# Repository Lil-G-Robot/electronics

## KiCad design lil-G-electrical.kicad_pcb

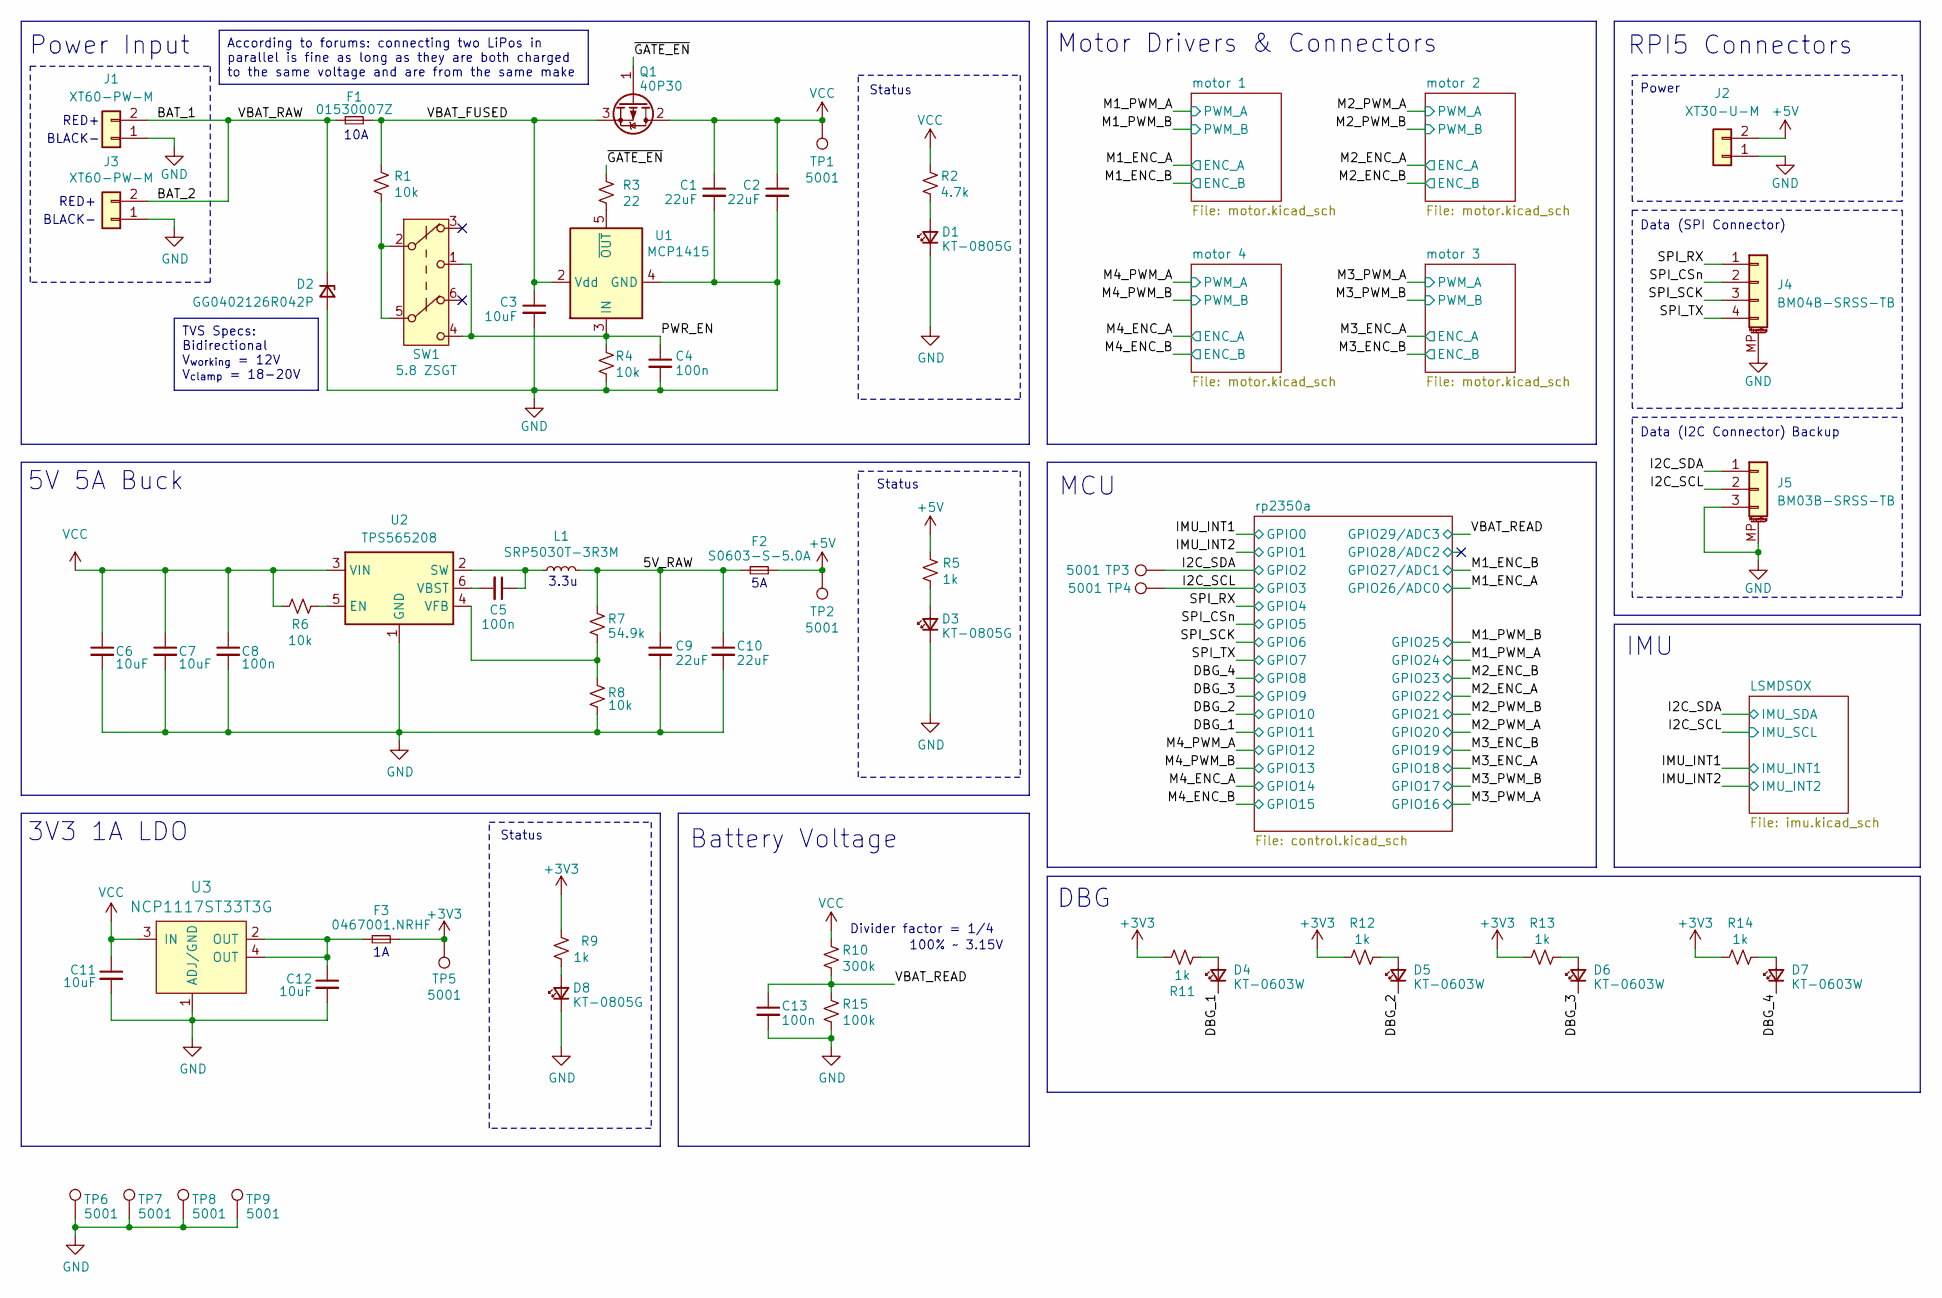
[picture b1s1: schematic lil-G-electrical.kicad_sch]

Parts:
C1, C2, C9, C10: 22uF; C_0805_2012Metric
C3, C6, C7, C11, C12: 10uF; C_0603_1608Metric
C4, C5, C8, C13: 100n; C_0402_1005Metric
D1, D3, D8: KT-0805G; LED_0805_2012Metric
D2: GG0402126R042P; D_0402_1005Metric
D4, D5, D6, D7: KT-0603W; LED_0603_1608Metric
F1: 01530007Z; LittleFuse_01530007Z
F2: S0603-S-5.0A; Fuse_0603_1608Metric; MPN F0603SB5000V032TM
F3: 0467001.NRHF; Fuse_0603_1608Metric; MPN F0603SB5000V032TM
J1, J3: XT60-PW-M; AMASS_XT60PW-M_1x02_P7.20mm_Horizontal
J2: XT30-U-M; AMASS_XT30U-M_1x02_P5.0mm_Vertical
J4: BM04B-SRSS-TB; JST_SH_BM04B-SRSS-TB_1x04-1MP_P1.00mm_Vertical
J5: BM03B-SRSS-TB; JST_SH_BM03B-SRSS-TB_1x03-1MP_P1.00mm_Vertical
L1: SRP5030T-3R3M; L_Bourns_SRP5030T; MPN SRP5030T-3R3M
Q1: 40P30; TO-252-2
R1, R4, R6, R8: 10k; R_0402_1005Metric
R2: 4.7k; R_0402_1005Metric
R3: 22; R_0402_1005Metric
R5, R9, R11, R12, R13, R14: 1k; R_0402_1005Metric
R7: 54.9k; R_0402_1005Metric
R10: 300k; R_0603_1608Metric
R15: 100k; R_0603_1608Metric
SW1: 5.8 ZSGT; 5.8_ZSGT
TP1, TP2, TP3, TP4, TP5, TP6, TP7, TP8, TP9: 5001; TestPoint_Keystone_5000-5004_Miniature
U1: MCP1415; SOT-23-5
U2: TPS565208; SOT-23-6
U3: NCP1117ST33T3G; SOT-223; MPN NCP1117ST33T3G

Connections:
+3V3: F3.2, R9.2, R11.1, R12.2, R13.2, R14.2, TP5.1; also elsewhere on the board
+5V: F2.2, J2.2, R5.2, TP2.1; also elsewhere on the board
/5V_RAW: C9.1, C10.1, F2.1, L1.2, R7.2
/BAT_1: D2.1 (K), F1.1, J1.2, J3.2
/DBG_1: D4.1 (K); also elsewhere on the board
/DBG_2: D5.1 (K); also elsewhere on the board
/DBG_3: D6.1 (K); also elsewhere on the board
/DBG_4: D7.1 (K); also elsewhere on the board
/I2C_SCL: J5.2, TP4.1; also elsewhere on the board
/I2C_SDA: J5.1, TP3.1; also elsewhere on the board
/PWR_EN: C4.1, R4.1, SW1.1 (C), SW1.4 (C), U1.3 (IN)
/SPI_CSn: J4.2; also elsewhere on the board
/SPI_RX: J4.1; also elsewhere on the board
/SPI_SCK: J4.3; also elsewhere on the board
/SPI_TX: J4.4; also elsewhere on the board
/VBAT_FUSED: C3.1, F1.2, Q1.3 (S), R1.1, U1.2 (Vdd)
/VBAT_READ: C13.1, R10.1, R15.2; also elsewhere on the board
/~GATE_EN: Q1.1 (G), R3.1
GND: C1.2, C2.2, C3.2, C4.2, C6.2, C7.2, C8.2, C9.2, C10.2, C11.2, C12.2, C13.2, D1.1 (K), D2.2 (A), D3.1 (K), D8.1 (K), J1.1, J2.1, J3.1, J4.MP (MountPin), J5.3, J5.MP (MountPin), R4.2, R8.1, R15.1, TP6.1, TP7.1, TP8.1, TP9.1, U1.4 (GND), U2.1 (GND), U3.1 (ADJ/GND); also elsewhere on the board
unnamed: C12.1, F3.1, U3.2 (OUT), U3.4 (OUT)
unnamed: D1.2 (A), R2.1
unnamed: D3.2 (A), R5.1
unnamed: D4.2 (A), R11.2
unnamed: D5.2 (A), R12.1
unnamed: D6.2 (A), R13.1
unnamed: D7.2 (A), R14.1
unnamed: D8.2 (A), R9.1
unnamed: R1.2, SW1.2 (B), SW1.5 (B)
unnamed: R3.2, U1.5 (~OUT)
unnamed: R6.1, U2.5 (EN)
unnamed: C5.1, L1.1, U2.2 (SW)
unnamed: C5.2, U2.6 (VBST)
unnamed: R7.1, R8.2, U2.4 (VFB)
VCC: C1.1, C2.1, C6.1, C7.1, C8.1, C11.1, Q1.2 (D), R2.2, R6.2, R10.2, TP1.1, U2.3 (VIN), U3.3 (IN); also elsewhere on the board

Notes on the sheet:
According to forums: connecting two LiPos in parallel is fine as long as they are both charged to the same voltage and are from the same make
TVS Specs: Bidirectional V_{working} = 12V V_{clamp} = 18-20V
RPI5 Connectors
IMU
Status
MCU
Data (SPI Connector)
5V 5A Buck
BLACK-
Divider factor = 1/4
100% ~ 3.15V
Power
Data (I2C Connector)
Battery Voltage
Motor Drivers & Connectors
Power Input
DBG
3V3 1A LDO
10A
RED+
Backup
3.3u

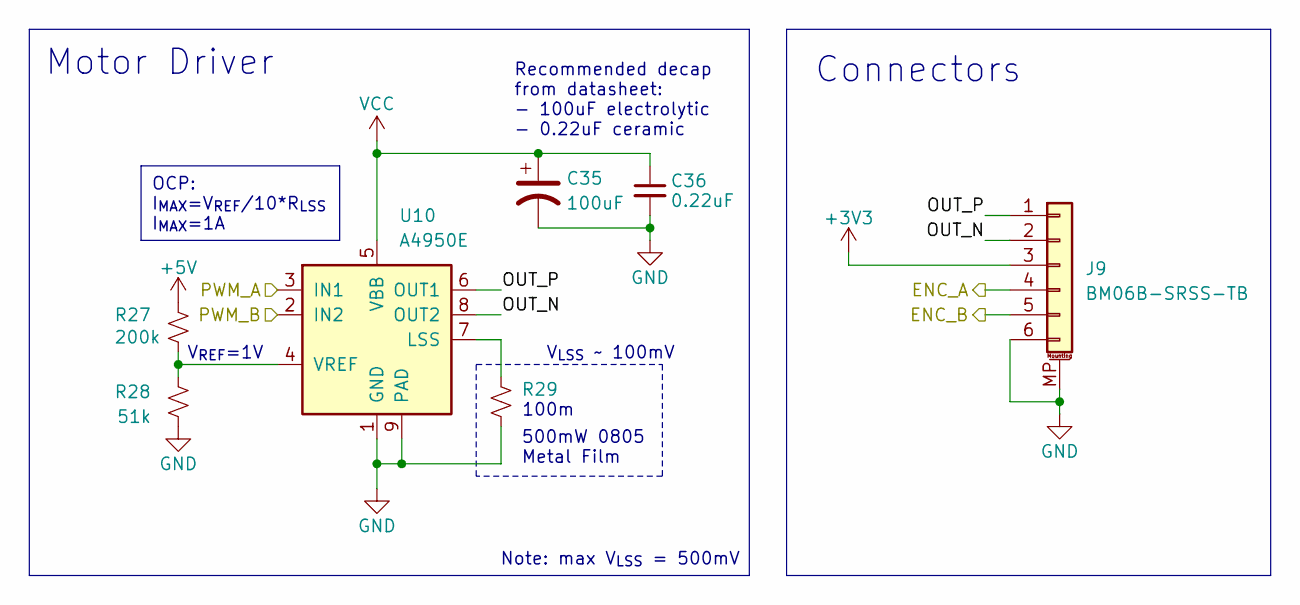
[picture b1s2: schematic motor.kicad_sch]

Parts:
C35: 100uF; CP_Elec_6.3x7.7
C36: 0.22uF; C_0603_1608Metric
J9: BM06B-SRSS-TB; JST_SH_BM06B-SRSS-TB_1x06-1MP_P1.00mm_Vertical
R27: 200k; R_0402_1005Metric
R28: 51k; R_0402_1005Metric
R29: RL10FTNR100; R_0805_2012Metric
U10: A4950E; SOIC-8-1EP_3.9x4.9mm_P1.27mm_EP2.41x3.3mm_ThermalVias

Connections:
+3V3: J9.3; also elsewhere on the board
+5V: R27.2; also elsewhere on the board
/M1_ENC_A: J9.4; also elsewhere on the board
/M1_ENC_B: J9.5; also elsewhere on the board
/M1_PWM_A: U10.3 (IN1); also elsewhere on the board
/M1_PWM_B: U10.2 (IN2); also elsewhere on the board
/motor 1/OUT_N: J9.2, U10.8 (OUT2)
/motor 1/OUT_P: J9.1, U10.6 (OUT1)
GND: C35.2, C36.2, J9.6, J9.MP (MountPin), R28.1, R29.2, U10.1 (GND), U10.9 (PAD); also elsewhere on the board
unnamed: R29.1, U10.7 (LSS)
unnamed: R27.1, R28.2, U10.4 (VREF)
VCC: C35.1, C36.1, U10.5 (VBB); also elsewhere on the board

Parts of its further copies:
C37, C39, C41: 100uF; CP_Elec_6.3x7.7
C38, C40, C42: 0.22uF; C_0603_1608Metric
J10, J11, J12: BM06B-SRSS-TB; JST_SH_BM06B-SRSS-TB_1x06-1MP_P1.00mm_Vertical
R30, R33, R36: 200k; R_0402_1005Metric
R32, R35, R38: RL10FTNR100; R_0805_2012Metric
U11, U12, U13: A4950E; SOIC-8-1EP_3.9x4.9mm_P1.27mm_EP2.41x3.3mm_ThermalVias

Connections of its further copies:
+3V3: J10.3, J11.3, J12.3; also elsewhere on the board
+5V: R30.2, R33.2, R36.2; also elsewhere on the board
/M2_ENC_A: J10.4; also elsewhere on the board
/M2_ENC_B: J10.5; also elsewhere on the board
/M2_PWM_A: U11.3 (IN1); also elsewhere on the board
/M2_PWM_B: U11.2 (IN2); also elsewhere on the board
/M3_ENC_A: J11.4; also elsewhere on the board
/M3_ENC_B: J11.5; also elsewhere on the board
/M3_PWM_A: U12.3 (IN1); also elsewhere on the board
/M3_PWM_B: U12.2 (IN2); also elsewhere on the board
/M4_ENC_A: J12.4; also elsewhere on the board
/M4_ENC_B: J12.5; also elsewhere on the board
/M4_PWM_A: U13.3 (IN1); also elsewhere on the board
/M4_PWM_B: U13.2 (IN2); also elsewhere on the board
/motor 2/OUT_N: J10.2, U11.8 (OUT2)
/motor 2/OUT_P: J10.1, U11.6 (OUT1)
/motor 3/OUT_N: J11.2, U12.8 (OUT2)
/motor 3/OUT_P: J11.1, U12.6 (OUT1)
/motor 4/OUT_N: J12.2, U13.8 (OUT2)
/motor 4/OUT_P: J12.1, U13.6 (OUT1)
GND: C37.2, C38.2, C39.2, C40.2, C41.2, C42.2, J10.6, J10.MP (MountPin), J11.6, J11.MP (MountPin), J12.6, J12.MP (MountPin), R32.2, R35.2, R38.2, U11.1 (GND), U11.9 (PAD), U12.1 (GND), U12.9 (PAD), U13.1 (GND), U13.9 (PAD); also elsewhere on the board
unnamed: R32.1, U11.7 (LSS)
unnamed 92: R30.1, U11.4 (VREF); also elsewhere on the board
unnamed: R35.1, U12.7 (LSS)
unnamed 94: R33.1, U12.4 (VREF); also elsewhere on the board
unnamed: R38.1, U13.7 (LSS)
unnamed 96: R36.1, U13.4 (VREF); also elsewhere on the board
VCC: C37.1, C38.1, C39.1, C40.1, C41.1, C42.1, U11.5 (VBB), U12.5 (VBB), U13.5 (VBB); also elsewhere on the board

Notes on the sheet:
OCP: I_{MAX}=V_{REF}/10*R_{LSS} I_{MAX}=1A
Recommended decap from datasheet: - 100uF electrolytic - 0.22uF ceramic
V_{REF}=1V
Connectors
100m
V_{LSS} ~ 100mV
Motor Driver
500mW 0805 Metal Film
Note: max V_{LSS} = 500mV

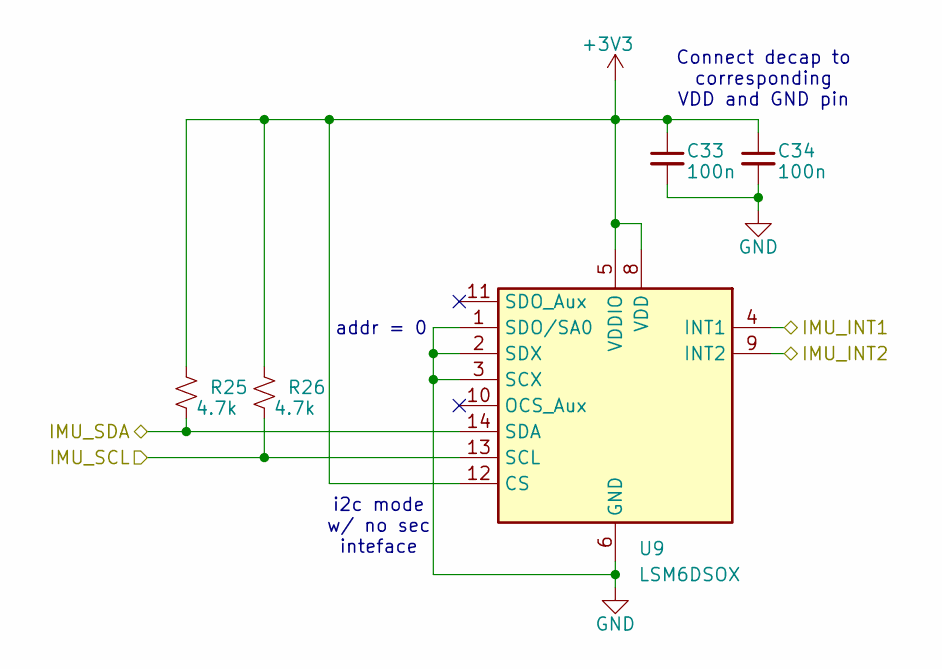
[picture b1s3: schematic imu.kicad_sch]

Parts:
C33, C34: 100n; C_0402_1005Metric
R25, R26: 4.7k; R_0402_1005Metric
U9: LSM6DSOX; LGA-14_3x2.5mm_P0.5mm_LayoutBorder3x4y

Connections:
+3V3: C33.1, C34.1, R25.2, R26.2, U9.5 (VDDIO), U9.8 (VDD), U9.12 (CS); also elsewhere on the board
/I2C_SCL: R26.1, U9.13 (SCL); also elsewhere on the board
/I2C_SDA: R25.1, U9.14 (SDA); also elsewhere on the board
/IMU_INT1: U9.4 (INT1); also elsewhere on the board
/IMU_INT2: U9.9 (INT2); also elsewhere on the board
GND: C33.2, C34.2, U9.1 (SDO/SA0), U9.2 (SDX), U9.3 (SCX), U9.6 (GND), U9.7 (GND); also elsewhere on the board

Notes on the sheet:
i2c mode w/ no sec inteface
Connect decap to corresponding VDD and GND pin
addr = 0

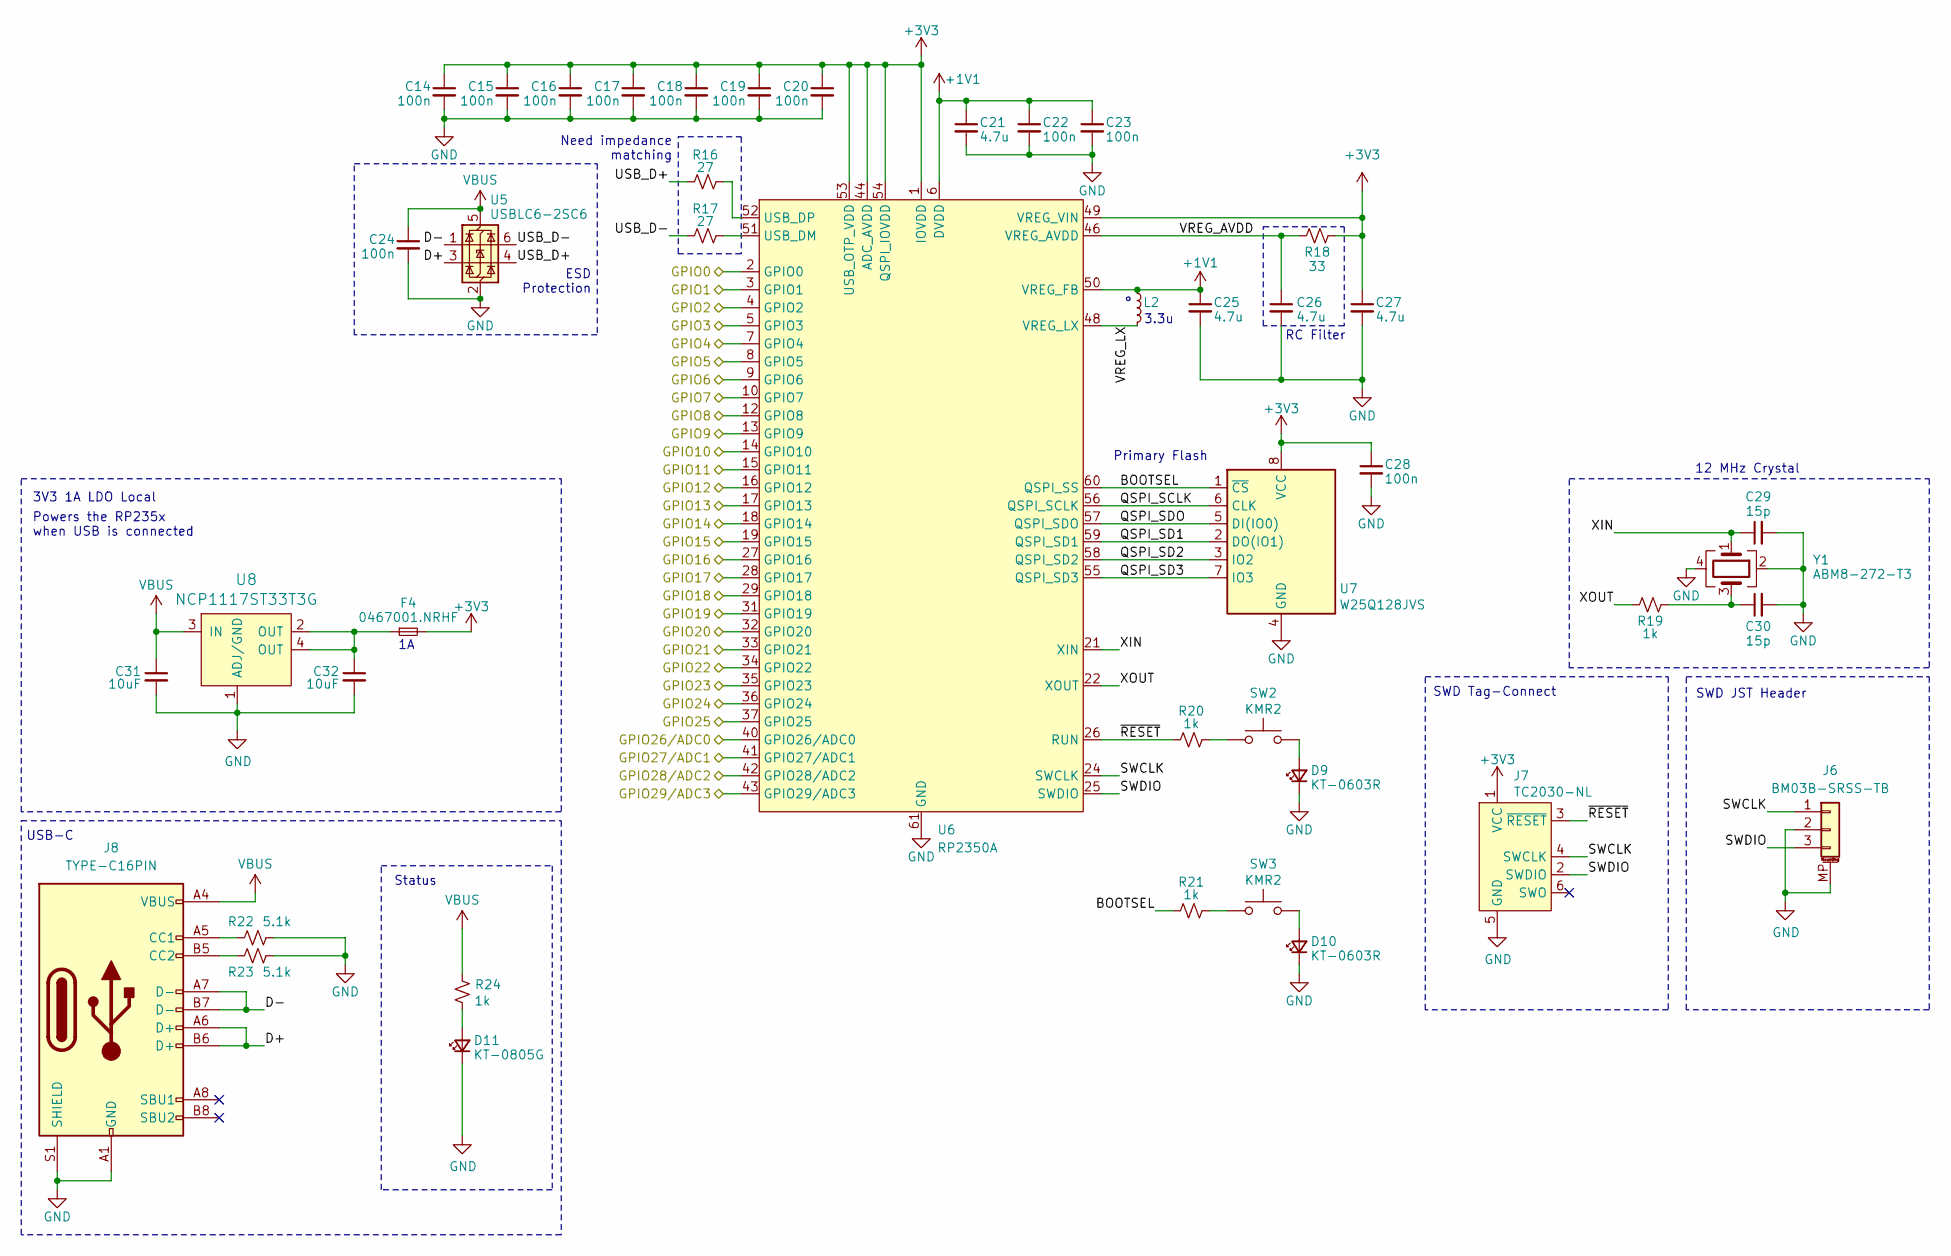
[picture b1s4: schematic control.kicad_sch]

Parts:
C14, C15, C16, C17, C18, C19, C20, C22, C23, C24, C28: 100n; C_0402_1005Metric
C21, C25, C26, C27: 4.7u; C_0402_1005Metric
C29, C30: 15p; C_0402_1005Metric
C31, C32: 10uF; C_0603_1608Metric
D9, D10: KT-0603R; LED_0603_1608Metric
D11: KT-0805G; LED_0805_2012Metric
F4: 0467001.NRHF; Fuse_0603_1608Metric; MPN F0603SB5000V032TM
J6: BM03B-SRSS-TB; JST_SH_BM03B-SRSS-TB_1x03-1MP_P1.00mm_Vertical
J7: TC2030-NL; Tag-Connect_TC2030-IDC-NL_2x03_P1.27mm_Vertical
J8: TYPE-C16PIN; USB_C_Receptacle_GCT_USB4105-xx-A_16P_TopMnt_Horizontal
L2: AOTA-B201610S3R3-101-T; L_0806
R16, R17: 27; R_0402_1005Metric
R18: 33; R_0402_1005Metric
R19, R20, R21, R24: 1k; R_0402_1005Metric
R22, R23: 5.1k; R_0402_1005Metric
SW2, SW3: KMR2; SW_Push_1P1T_NO_CK_KMR2
U5: USBLC6-2SC6; SOT-23-6
U6: RP2350A; QFN-60-1EP_7x7mm_P0.4mm_EP3.4x3.4mm_ThermalVias
U7: W25Q128JVS; SOIC-8_5.23x5.23mm_P1.27mm
U8: NCP1117ST33T3G; SOT-223; MPN NCP1117ST33T3G
Y1: ABM8-272-T3; Crystal_SMD_Abracon_ABM8G-4Pin_3.2x2.5mm

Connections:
+1V1: C21.1, C22.1, C23.1, C25.1, L2.1, U6.6 (DVDD), U6.23 (DVDD), U6.39 (DVDD), U6.50 (VREG_FB)
+3V3: C14.1, C15.1, C16.1, C17.1, C18.1, C19.1, C20.1, C27.1, C28.1, F4.2, J7.1 (VCC), R18.2, U6.1 (IOVDD), U6.11 (IOVDD), U6.20 (IOVDD), U6.30 (IOVDD), U6.38 (IOVDD), U6.44 (ADC_AVDD), U6.45 (IOVDD), U6.49 (VREG_VIN), U6.53 (USB_OTP_VDD), U6.54 (QSPI_IOVDD), U7.8 (VCC); also elsewhere on the board
/DBG_1: U6.15 (GPIO11); also elsewhere on the board
/DBG_2: U6.14 (GPIO10); also elsewhere on the board
/DBG_3: U6.13 (GPIO9); also elsewhere on the board
/DBG_4: U6.12 (GPIO8); also elsewhere on the board
/I2C_SCL: U6.5 (GPIO3); also elsewhere on the board
/I2C_SDA: U6.4 (GPIO2); also elsewhere on the board
/IMU_INT1: U6.2 (GPIO0); also elsewhere on the board
/IMU_INT2: U6.3 (GPIO1); also elsewhere on the board
/M1_ENC_A: U6.40 (GPIO26/ADC0); also elsewhere on the board
/M1_ENC_B: U6.41 (GPIO27/ADC1); also elsewhere on the board
/M1_PWM_A: U6.36 (GPIO24); also elsewhere on the board
/M1_PWM_B: U6.37 (GPIO25); also elsewhere on the board
/M2_ENC_A: U6.34 (GPIO22); also elsewhere on the board
/M2_ENC_B: U6.35 (GPIO23); also elsewhere on the board
/M2_PWM_A: U6.32 (GPIO20); also elsewhere on the board
/M2_PWM_B: U6.33 (GPIO21); also elsewhere on the board
/M3_ENC_A: U6.29 (GPIO18); also elsewhere on the board
/M3_ENC_B: U6.31 (GPIO19); also elsewhere on the board
/M3_PWM_A: U6.27 (GPIO16); also elsewhere on the board
/M3_PWM_B: U6.28 (GPIO17); also elsewhere on the board
/M4_ENC_A: U6.18 (GPIO14); also elsewhere on the board
/M4_ENC_B: U6.19 (GPIO15); also elsewhere on the board
/M4_PWM_A: U6.16 (GPIO12); also elsewhere on the board
/M4_PWM_B: U6.17 (GPIO13); also elsewhere on the board
/SPI_CSn: U6.8 (GPIO5); also elsewhere on the board
/SPI_RX: U6.7 (GPIO4); also elsewhere on the board
/SPI_SCK: U6.9 (GPIO6); also elsewhere on the board
/SPI_TX: U6.10 (GPIO7); also elsewhere on the board
/VBAT_READ: U6.43 (GPIO29/ADC3); also elsewhere on the board
/rp2350a/BOOTSEL: R21.1, U6.60 (QSPI_SS), U7.1 (~CS)
/rp2350a/D+: J8.A6 (D+), J8.B6 (D+), U5.3 (I/O2)
/rp2350a/D-: J8.A7 (D-), J8.B7 (D-), U5.1 (I/O1)
/rp2350a/GPIO28/ADC2: U6.42 (GPIO28/ADC2)
/rp2350a/QSPI_SCLK: U6.56 (QSPI_SCLK), U7.6 (CLK)
/rp2350a/QSPI_SD1: U6.59 (QSPI_SD1), U7.2 (DO(IO1))
/rp2350a/QSPI_SD2: U6.58 (QSPI_SD2), U7.3 (IO2)
/rp2350a/QSPI_SD3: U6.55 (QSPI_SD3), U7.7 (IO3)
/rp2350a/QSPI_SDO: U6.57 (QSPI_SDO), U7.5 (DI(IO0))
/rp2350a/SWCLK: J6.1, J7.4 (SWCLK), U6.24 (SWCLK)
/rp2350a/SWDIO: J6.3, J7.2 (SWDIO), U6.25 (SWDIO)
/rp2350a/USB_D+: R16.1, U5.4 (I/O2)
/rp2350a/USB_D-: R17.1, U5.6 (I/O1)
/rp2350a/VREG_AVDD: C26.1, R18.1, U6.46 (VREG_AVDD)
/rp2350a/VREG_LX: L2.2, U6.48 (VREG_LX)
/rp2350a/XIN: C29.1, U6.21 (XIN), Y1.1
/rp2350a/XOUT: R19.1, U6.22 (XOUT)
/rp2350a/~RESET: J7.3 (~RESET), R20.1, U6.26 (RUN)
GND: C14.2, C15.2, C16.2, C17.2, C18.2, C19.2, C20.2, C21.2, C22.2, C23.2, C24.2, C25.2, C26.2, C27.2, C28.2, C29.2, C30.2, C31.2, C32.2, D9.1 (K), D10.1 (K), D11.1 (K), J6.2, J6.MP (MountPin), J7.5 (GND), J8.A1 (GND), J8.A12 (GND), J8.B1 (GND), J8.B12 (GND), J8.S1 (SHIELD), R22.2, R23.2, U5.2 (GND), U6.47 (VREG_PGND), U6.61 (GND), U7.4 (GND), U8.1 (ADJ/GND), Y1.2, Y1.4; also elsewhere on the board
unnamed: C30.1, R19.2, Y1.3
unnamed: C32.1, F4.1, U8.2 (OUT), U8.4 (OUT)
unnamed: D9.2 (A), SW2.2
unnamed: D10.2 (A), SW3.2
unnamed: D11.2 (A), R24.1
unnamed: J8.A5 (CC1), R22.1
unnamed: J8.B5 (CC2), R23.1
unnamed: R20.2, SW2.1
unnamed: R21.2, SW3.1
unnamed: R17.2, U6.51 (USB_DM)
unnamed: R16.2, U6.52 (USB_DP)
VBUS: C24.1, C31.1, J8.A4 (VBUS), J8.A9 (VBUS), J8.B4 (VBUS), J8.B9 (VBUS), R24.2, U5.5 (VBUS), U8.3 (IN)

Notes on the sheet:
SWD Tag-Connect
3.3u
Status
RC Filter
Primary Flash
ESD Protection
Need impedance matching
3V3 1A LDO Local
USB-C
12 MHz Crystal
Powers the RP235x when USB is connected
SWD JST Header

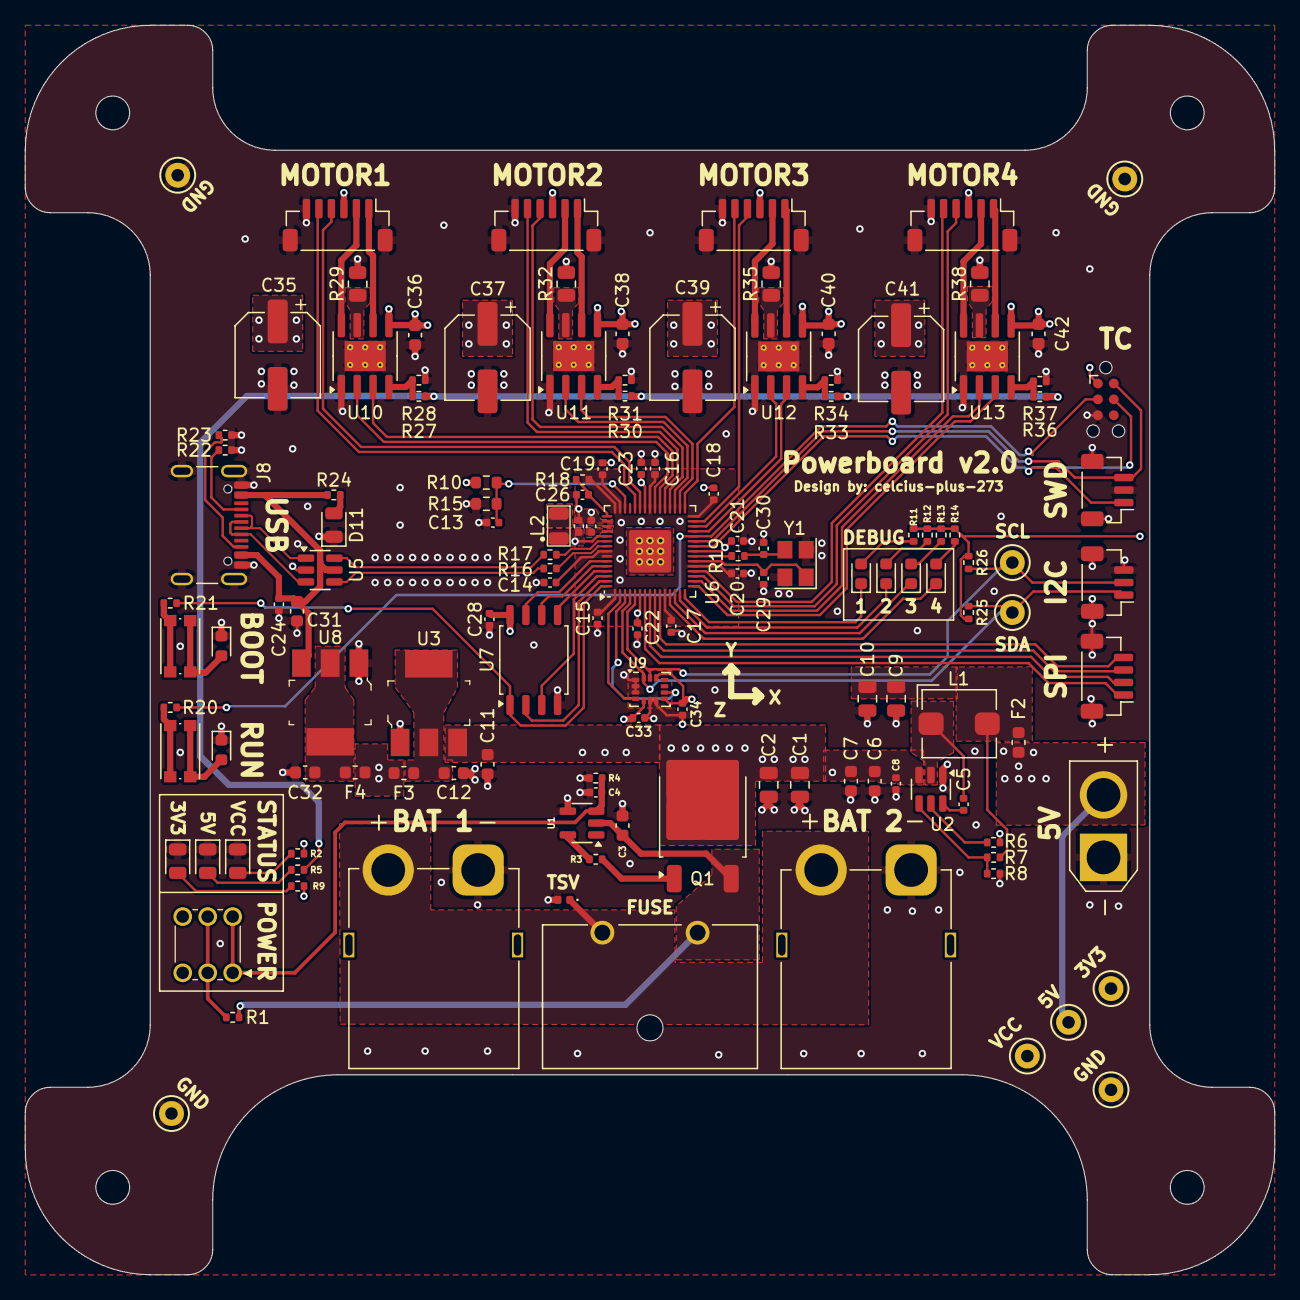
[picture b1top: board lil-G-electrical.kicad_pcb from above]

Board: 4 copper layers, 100.0 x 100.0 mm, 139 parts (0 on the bottom side), 98 nets.

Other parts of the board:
MH1, MH2, MH3, MH4: MountingHole_2.7mm_M2.5
R31, R34, R37: 50k; R_0402_1005Metric

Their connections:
GND: R31.1, R34.1, R37.1; also elsewhere on the board
unnamed 92: R31.2; also elsewhere on the board
unnamed 94: R34.2; also elsewhere on the board
unnamed 96: R37.2; also elsewhere on the board

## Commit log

2025-04-06 power input and regulation almost done
2025-04-07 small update on schematic
2025-04-13 finished layout of dc drivers and power regulation
2025-04-29 changed dimension of current sense resistor
2025-05-02 fixed high-side power enable circuit. flipped PMOS source/drain
2025-05-09 version 2 done
2025-05-09 deleted some unecessary files
2025-05-14 no idea what I updated
2025-05-18 made some changes
2025-05-18 last modification for v2.0 before submitting order
